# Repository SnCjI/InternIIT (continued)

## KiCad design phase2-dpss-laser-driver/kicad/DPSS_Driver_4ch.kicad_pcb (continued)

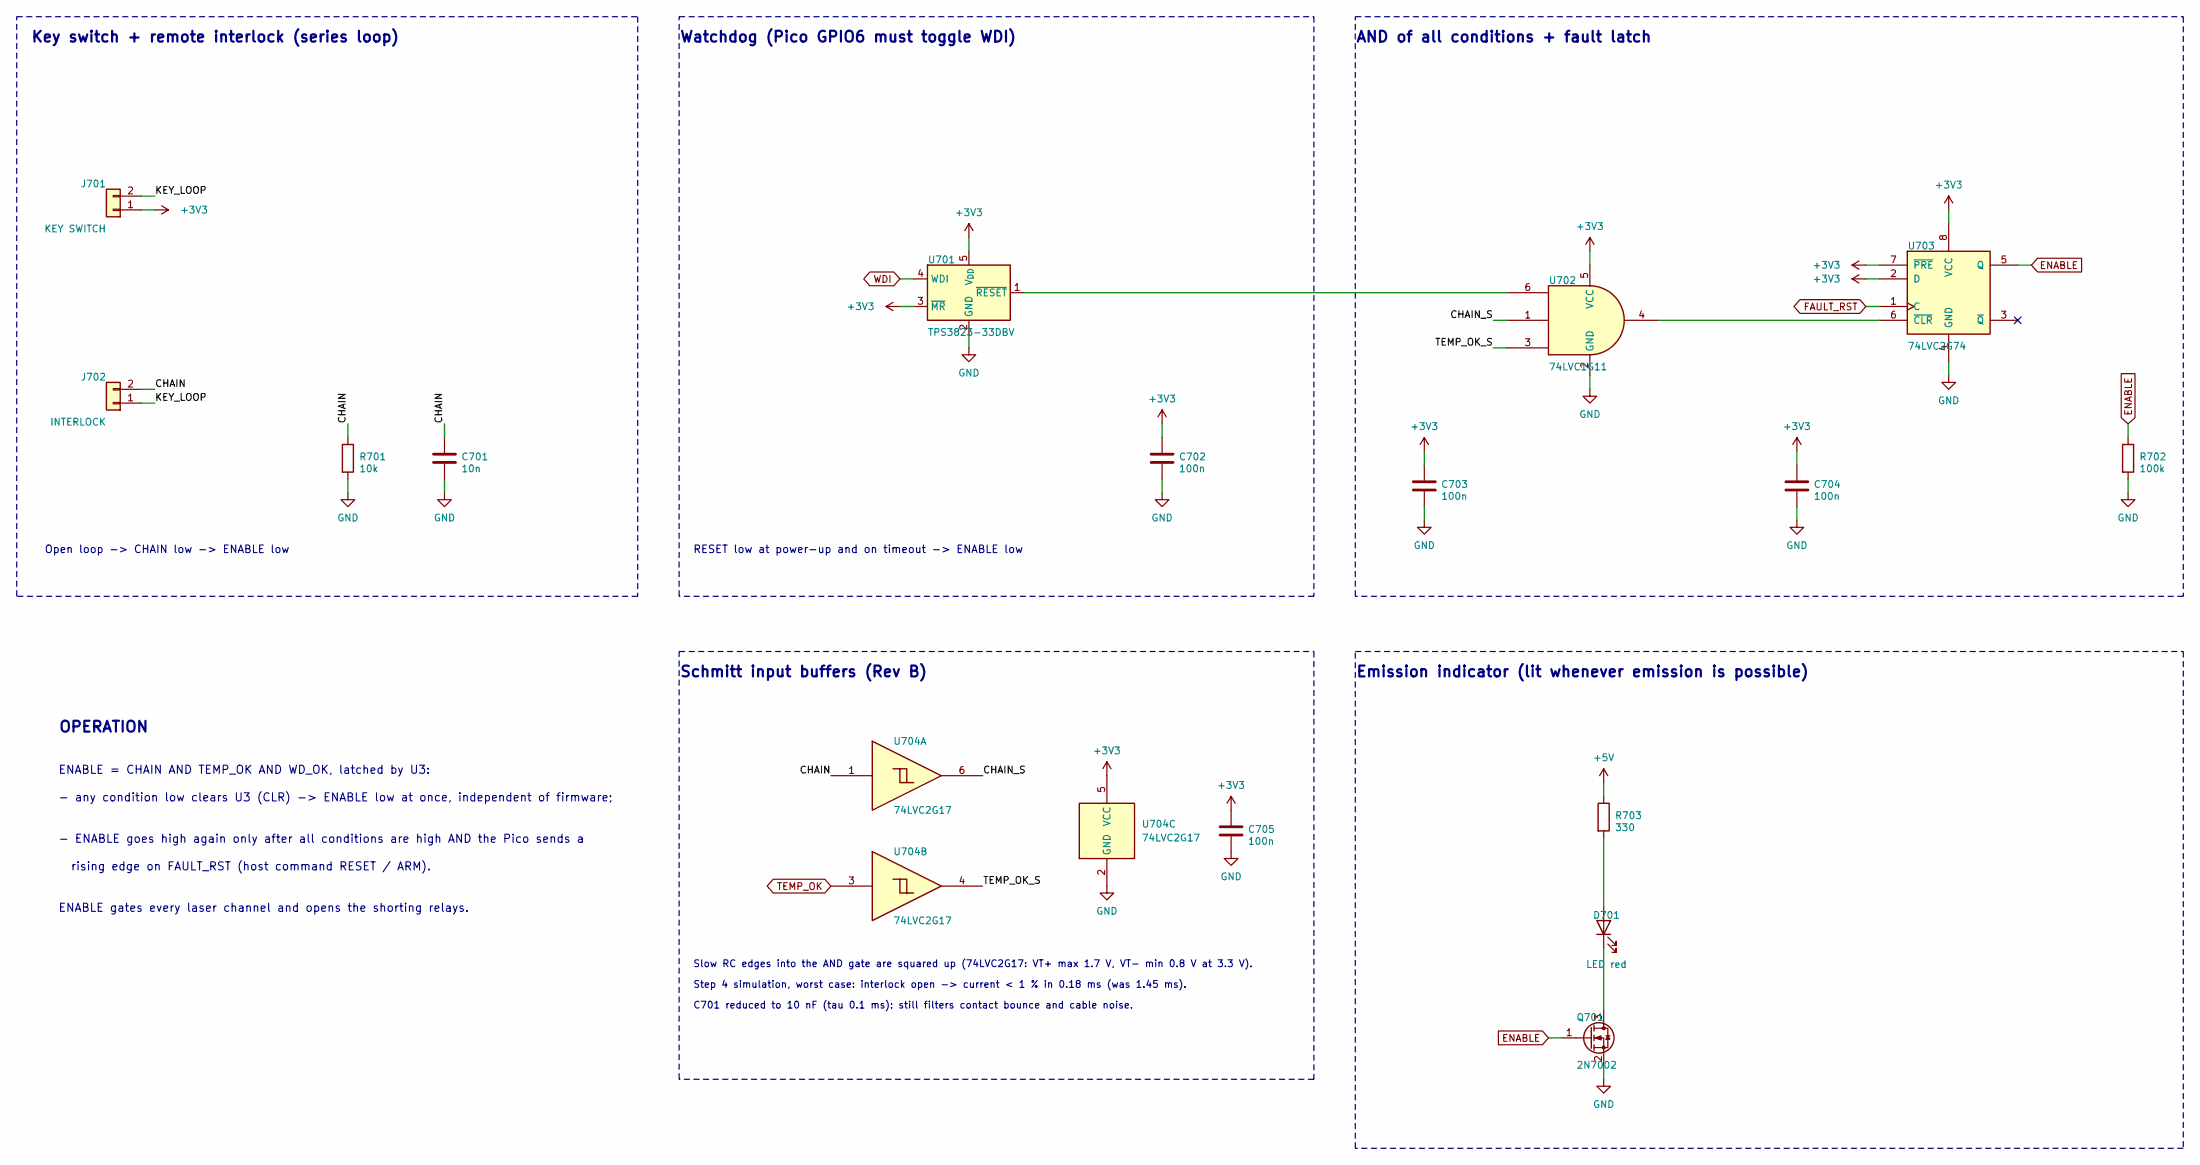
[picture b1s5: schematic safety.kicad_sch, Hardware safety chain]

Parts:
C701: 10n; C_0805_2012Metric
C702, C703, C704, C705: 100n; C_0805_2012Metric
D701: LED red; LED_0805_2012Metric
J701: KEY SWITCH; JST_XH_B2B-XH-A_1x02_P2.50mm_Vertical
J702: INTERLOCK; JST_XH_B2B-XH-A_1x02_P2.50mm_Vertical
Q701: 2N7002; SOT-23
R701: 10k; R_0805_2012Metric
R702: 100k; R_0805_2012Metric
R703: 330; R_0805_2012Metric
U701: TPS3823-33DBV; SOT-23-5
U702: 74LVC1G11; SOT-23-6
U703: 74LVC2G74; VSSOP-8_2.3x2mm_P0.5mm
U704: 74LVC2G17; SOT-23-6

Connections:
+3V3: C702.1, C703.1, C704.1, C705.1, J701.1, U701.3 (~MR), U701.5 (V_{DD}), U702.5 (VCC), U703.2 (D), U703.7 (~PRE), U703.8 (VCC), U704.5 (VCC); also elsewhere on the board
+5V: R703.1; also elsewhere on the board
/Safety/CHAIN: C701.1, J702.2, R701.1, U704.1
/Safety/CHAIN_S: U702.1, U704.6
/Safety/KEY_LOOP: J701.2, J702.1
/Safety/TEMP_OK_S: U702.3, U704.4
ENABLE: Q701.1 (G), R702.1, U703.5 (Q); also elsewhere on the board
FAULT_RST: U703.1 (C); also elsewhere on the board
GND: C701.2, C702.2, C703.2, C704.2, C705.2, Q701.2 (S), R701.2, R702.2, U701.2 (GND), U702.2 (GND), U703.4 (GND), U704.2 (GND); also elsewhere on the board
unnamed: D701.2 (A), R703.2
unnamed: D701.1 (K), Q701.3 (D)
unnamed: U701.1 (~RESET), U702.6
unnamed: U702.4, U703.6 (~CLR)
TEMP_OK: U704.3; also elsewhere on the board
WDI: U701.4 (WDI); also elsewhere on the board

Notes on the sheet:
OPERATION
AND of all conditions + fault latch
Emission indicator (lit whenever emission is possible)
- any condition low clears U3 (CLR) -> ENABLE low at once, independent of firmware;
rising edge on FAULT_RST (host command RESET / ARM).
ENABLE gates every laser channel and opens the shorting relays.
ENABLE = CHAIN AND TEMP_OK AND WD_OK, latched by U3:
Watchdog (Pico GPIO6 must toggle WDI)
RESET low at power-up and on timeout -> ENABLE low
Open loop -> CHAIN low -> ENABLE low
Key switch + remote interlock (series loop)
- ENABLE goes high again only after all conditions are high AND the Pico sends a
Schmitt input buffers (Rev B)
Slow RC edges into the AND gate are squared up (74LVC2G17: VT+ max 1.7 V, VT- min 0.8 V at 3.3 V).
Step 4 simulation, worst case: interlock open -> current < 1 % in 0.18 ms (was 1.45 ms).
C701 reduced to 10 nF (tau 0.1 ms): still filters contact bounce and cable noise.

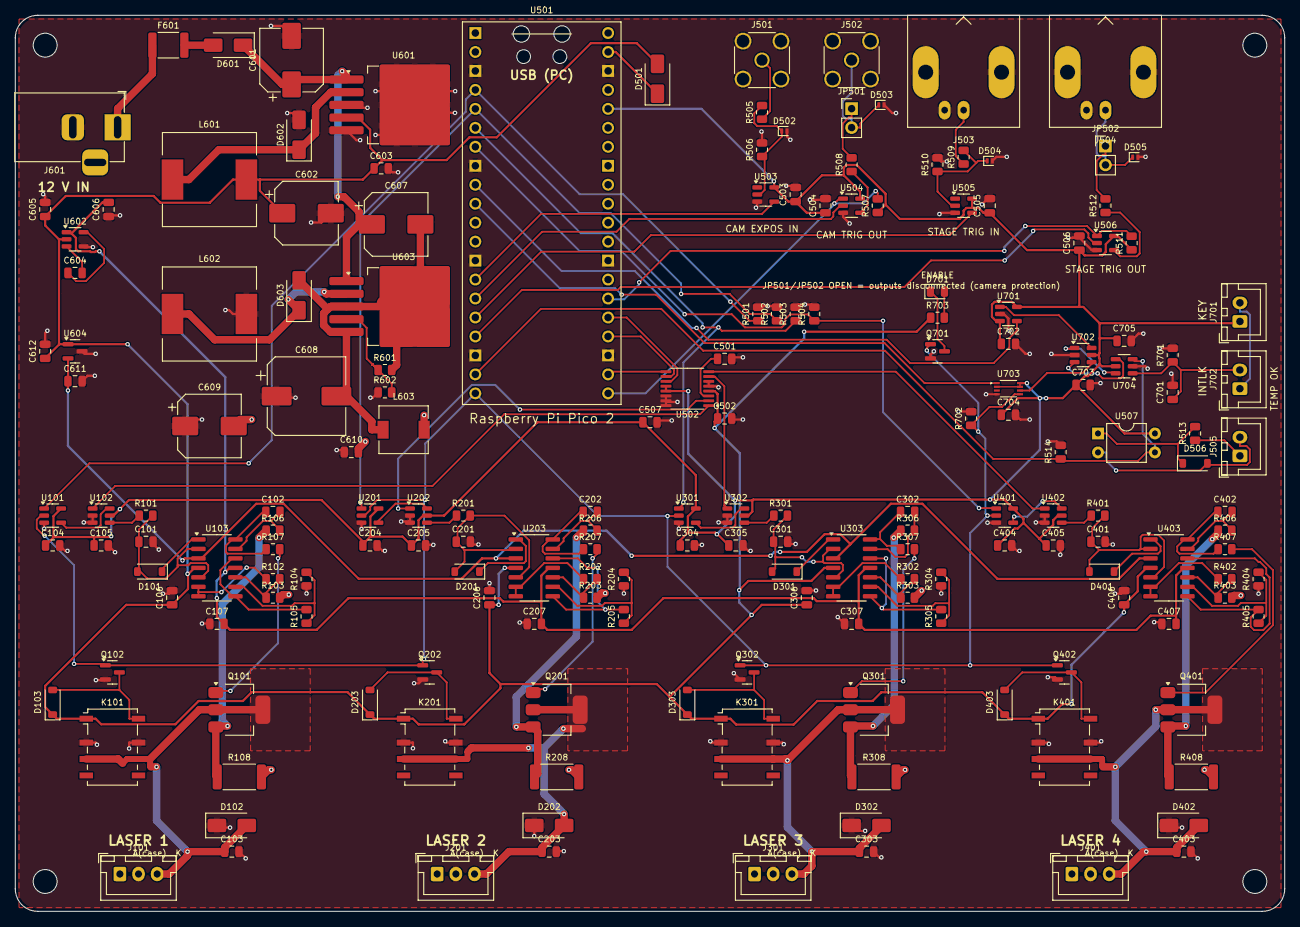
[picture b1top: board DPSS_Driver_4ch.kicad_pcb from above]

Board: 4 copper layers, 170.0 x 120.0 mm, 187 parts (0 on the bottom side), 115 nets.

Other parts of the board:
H1, H2, H3, H4: M3; MountingHole_3.2mm_M3

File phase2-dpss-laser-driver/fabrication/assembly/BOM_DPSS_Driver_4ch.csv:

Qty,Value,Footprint,References
8,2.2n C0G,Capacitor_SMD:C_0805_2012Metric,C101 C102 C201 C202 C301 C302 C401 C402
4,1n,Capacitor_SMD:C_0805_2012Metric,C103 C203 C303 C403
30,100n,Capacitor_SMD:C_0805_2012Metric,C104 C105 C106 C107 C204 C205 C206 C207 C304 C305 C306 C307 C404 C405 C406 C407 C501 C502 C503 C504 C505 C506 C507 C603 C610 C612 C702 C703 C704 C705
1,10n,Capacitor_SMD:C_0805_2012Metric,C701
1,100u 25V,Capacitor_SMD:CP_Elec_8x10,C601
2,220u 10V,Capacitor_SMD:CP_Elec_8x10,C602 C609
4,1u,Capacitor_SMD:C_0805_2012Metric,C604 C605 C606 C611
1,100u 35V,Capacitor_SMD:CP_Elec_8x10,C607
1,470u 10V,Capacitor_SMD:CP_Elec_10x10,C608
9,1N4148W,Diode_SMD:D_SOD-123,D101 D103 D201 D203 D301 D303 D401 D403 D506
5,SS14,Diode_SMD:D_SMA,D102 D202 D302 D402 D501
2,PESD3V3S1UL,Diode_SMD:D_SOD-882,D502 D503
2,PESD5V0L1UL,Diode_SMD:D_SOD-882,D504 D505
3,SS34,Diode_SMD:D_SMA,D601 D602 D603
1,LED red,LED_SMD:LED_0805_2012Metric,D701
1,2 A,Fuse:Fuse_1812_4532Metric,F601
4,LASER (JST-XH),Connector_JST:JST_XH_B3B-XH-A_1x03_P2.50mm_Vertical,J101 J201 J301 J401
2,SMA,Connector_Coaxial:SMA_Amphenol_132134_Vertical,J501 J502
2,BNC,Connector_Coaxial:BNC_Amphenol_B6252HB-NPP3G-50_Horizontal,J503 J504
1,TEMP_OK IN,Connector_JST:JST_XH_B2B-XH-A_1x02_P2.50mm_Vertical,J505
1,12 V IN,Connector_BarrelJack:BarrelJack_Horizontal,J601
1,KEY SWITCH,Connector_JST:JST_XH_B2B-XH-A_1x02_P2.50mm_Vertical,J701
1,INTERLOCK,Connector_JST:JST_XH_B2B-XH-A_1x02_P2.50mm_Vertical,J702
2,OPEN,Connector_PinHeader_2.54mm:PinHeader_1x02_P2.54mm_Vertical,JP501 JP502
4,G6K-2F-Y 5V,Relay_SMD:Relay_DPDT_Omron_G6K-2F-Y,K101 K201 K301 K401
2,33u 3A,Inductor_SMD:L_12x12mm_H8mm,L601 L602
1,10u 3A,Inductor_SMD:L_6.3x6.3_H3,L603
4,NDT3055L,Package_TO_SOT_SMD:SOT-223-3_TabPin2,Q101 Q201 Q301 Q401
5,2N7002,Package_TO_SOT_SMD:SOT-23,Q102 Q202 Q302 Q402 Q701
10,1k,Resistor_SMD:R_0805_2012Metric,R101 R106 R201 R206 R301 R306 R401 R406 R509 R513
8,100k 0.1%,Resistor_SMD:R_0805_2012Metric,R102 R104 R202 R204 R302 R304 R402 R404
8,16k 0.1%,Resistor_SMD:R_0805_2012Metric,R103 R105 R203 R205 R303 R305 R403 R405
4,47,Resistor_SMD:R_0805_2012Metric,R107 R207 R307 R407
4,1R 0.1% 1W,Resistor_SMD:R_2512_6332Metric,R108 R208 R308 R408
7,100k,Resistor_SMD:R_0805_2012Metric,R501 R502 R503 R504 R506 R510 R702
3,100,Resistor_SMD:R_0805_2012Metric,R505 R508 R512
4,10k,Resistor_SMD:R_0805_2012Metric,R507 R511 R514 R701
1,1k 1%,Resistor_SMD:R_0805_2012Metric,R601
1,1.69k 1%,Resistor_SMD:R_0805_2012Metric,R602
1,330,Resistor_SMD:R_0805_2012Metric,R703
4,74LVC1G08,Package_TO_SOT_SMD:SOT-23-5,U101 U201 U301 U401
4,TS5A3159,Package_TO_SOT_SMD:SOT-23-6,U102 U202 U302 U402
4,OPA4197,Package_SO:SOIC-14_3.9x8.7mm_P1.27mm,U103 U203 U303 U403
1,Raspberry Pi Pico 2,Module:RaspberryPi_Pico_Common_Unspecified,U501
1,DAC8565,Package_SO:TSSOP-16_4.4x5mm_P0.65mm,U502
2,74LVC1G17,Package_TO_SOT_SMD:SOT-23-5,U503 U505
2,74LVC1G125,Package_TO_SOT_SMD:SOT-23-5,U504 U506
1,PC817,Package_DIP:DIP-4_W7.62mm,U507
1,LM2596S-5.0,Package_TO_SOT_SMD:TO-263-5_TabPin3,U601
1,TPS60403,Package_TO_SOT_SMD:SOT-23-5,U602
1,LM2596S-ADJ,Package_TO_SOT_SMD:TO-263-5_TabPin3,U603
1,REF3025,Package_TO_SOT_SMD:SOT-23,U604
1,TPS3823-33DBV,Package_TO_SOT_SMD:SOT-23-5,U701
1,74LVC1G11,Package_TO_SOT_SMD:SOT-23-6,U702
1,74LVC2G74,Package_SO:VSSOP-8_2.3x2mm_P0.5mm,U703
1,74LVC2G17,Package_TO_SOT_SMD:SOT-23-6,U704

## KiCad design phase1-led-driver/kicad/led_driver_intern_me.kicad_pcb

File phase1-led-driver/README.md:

# Phase 1 — Five-Channel Multispectral LED Driver

**ESP32 PWM control · MEAN WELL LDD-H constant-current modules · KiCad 10 · Proteus / ngspice**

Phase 1 of the internship: a driver that powers five high-power COB LEDs (UV, Blue, Green, Red and NIR) for multispectral microscopy. Each color can be dimmed independently from a PC. The design was taken from requirements to a fabrication-ready PCB and verified in simulation. No hardware was built.

Full report (IEEE format): [`report/Multispectral_LED_Driver_Phase1_Report_IEEE.pdf`](report/Multispectral_LED_Driver_Phase1_Report_IEEE.pdf)

<p align="center">
  
  <br><em>One channel k: ESP32 PWM → NPN buffer → LDD-H constant-current module → COB LED. There are five of these.</em>
</p>

---

## How it works

High-power LEDs have to be driven with **constant current**, not constant voltage. Their forward voltage changes with temperature and from part to part, so a fixed voltage would give each channel a different brightness and could cause thermal runaway.

The design splits the job in two:

- **The LDD-H module regulates the current.** This is a MEAN WELL step-down constant-current driver (350, 500 or 700 mA versions). It holds the LED current steady whatever happens to the supply.
- **The ESP32 decides how long the current flows.** Its LEDC hardware peripheral produces a 500 Hz, 10-bit PWM signal on each channel (GPIO 4, 5, 18, 19, 21). The LED is either fully on at its rated current or fully off, so the **average** current is

  **I<sub>avg</sub> = D · I<sub>on</sub>**, where D is the duty cycle.

A P2N2222A transistor sits between each GPIO and the LDD-H DIM input. It isolates the 3.3 V microcontroller from the module, but it also **inverts** the signal: GPIO high → DIM pulled low → LED off. The firmware compensates by writing `1023 − duty`.

A nice side effect of PWM dimming is that the LED always runs at its full rated current while it is on, so its emission spectrum does not shift as the brightness changes. That matters for multispectral imaging.

---

## Step by step: what was done

### Step 1 — Requirements and architecture

I wrote down eight requirements (R1–R8) and linked each one to a test case: five independent channels, 0–100 % intensity, constant current (350–700 mA), a single 12 V supply with a 3.3 V logic interface, a serial command interface, hardware PWM with less than 1 LSB of timing error, a clean two-layer PCB, and thermal margin for every part.

### Step 2 — Schematic and design review

The schematic repeats the same block five times: a 1 kΩ base resistor, a P2N2222A transistor, a 6-pin header for the LDD-H module (J0–J4), and the LED output pads (D0–D4). An 8-pin header (J5) brings in +12 V, GND and the five PWM signals.

Before drawing the PCB I reviewed every connection against the datasheets. **This review found four groups of defects**, two of which would have made the board useless:

| Problem found | Fix |
|---|---|
| The PCB file I inherited contained only graphics (0 pads, 0 nets) | Regenerated the board from the schematic and routed it from scratch |
| The generic NPN symbol used B-C-E pin order, but the P2N2222A TO-92 package is **C-B-E** | Changed to the correct symbol, so base and collector are no longer swapped |
| LEDs D0–D4 were wired with **reversed polarity** | Swapped the VOUT+/VOUT− labels |
| Net-label errors (global vs. local, an undefined net, duplicate connectors) | Unified the labels and aligned references with the PCB |

Result: **KiCad ERC, 0 errors.**

### Step 3 — PCB layout

- Two layers, FR-4, 1.6 mm, 1 oz copper, **118 × 43 mm**, through-hole parts only for easy hand assembly
- Each channel sits in an identical 20 mm cell: header, transistor, resistor, LED
- +12 V bus on top and ground bus on the bottom, both 0.8 mm wide
- No vias needed: 77 pads, 91 track segments, 27 nets
- Silkscreen labels for every J5 pin and every channel color

Result: **KiCad DRC, 0 violations, 0 unconnected items, 0 schematic-parity differences.**

### Step 4 — Firmware

[`firmware/firmware_intern/firmware_intern.ino`](firmware/firmware_intern/firmware_intern.ino) is an Arduino sketch for the ESP32 (Arduino core 3.x; the code has a note on the 2.x API). It accepts text commands at 115200 baud:

| Command | Effect |
|---|---|
| `SET <ch 0–4> <duty 0–100>` | Set one channel's brightness |
| `ALL <duty 0–100>` | Set every channel |
| `OFF` | Turn every channel off |
| `STATUS` | Show name, GPIO and duty of each channel |
| `HELP` | List the commands |

All channels start at `MAX_DUTY`, so the LEDs turn off as soon as the firmware runs. The sketch was run in the **Velxio ESP32 simulator** and passed every command test.

### Step 5 — Circuit simulation

The LDD-H is a sealed module with no public SPICE model, so I simulated each half of the channel with an equivalent circuit, then both halves together:

**a) Constant-current regulation.** A classic two-transistor current limiter was simulated in Proteus while the supply was swept from 8 V to 15 V. The current stayed at **0.48–0.50 A** (within ±0.01 A, which is the resolution of the simulated ammeter).

**b) PWM buffer switching.** The transistor stage turns the 0–3.3 V PWM into a clean 0–5 V inverted DIM signal. The worst edge delay is about **0.17 µs**, under 0.1 LSB of the 10-bit PWM period (1 LSB = 1.96 µs), so it does not affect brightness resolution.

**c) Duty cycle → LED current.** Both halves were joined in one test bench and run at D = 0, 5, 20, 50, 80 and 100 %. The on-current is always 363 mA. Only the fraction of time it flows changes, and the average follows **I<sub>avg</sub> = D · I<sub>on</sub>** with a constant offset of only −0.7 mA (about 2 LSB). An ngspice sweep from 0 to 100 % confirms the same straight line.

### Step 6 — Thermal check and test report

Every part on the board runs far below its rating: the transistors dissipate less than 2 mW each, and the 0.8 mm power traces heat up about 4 °C at full load. The real heat sources are the COB LEDs (about 3 W each), which have to be mounted off-board on a heatsink.

The test report has **15 test cases; 14 pass**. The one "fail" (TC-14) is intentional. It shows that the discrete limiter used for simulation would overheat as real hardware (5.5 W in a TO-92 package), which is exactly why the real design uses the LDD-H module.

### Step 7 — Fabrication package

Everything needed to order the board is in [`fabrication/`](fabrication/). For one-click ordering, the ready-made package is [`LED_Driver_5ch_Fabrication_Package_v1.0.zip`](fabrication/LED_Driver_5ch_Fabrication_Package_v1.0.zip).

| Folder | Content |
|---|---|
| `gerbers/` | Gerber X2 (copper, mask, paste, silkscreen, outline), job file, Excellon PTH + NPTH |
| `assembly/` | BOM (5× P2N2222A, 5× 1 kΩ, 5× 1×6 header, 1× 1×8 header, LED positions) and placement file |
| `docs/` | Schematic PDF, Gerber preview, DRC screenshot |
| `README_fabrication.txt` | Board specs and **assembly warnings**: use the P2N2222A (not PN2222A), the square pad is the LED cathode, and don't fit 5 mm LEDs while an LDD-H is installed |

---

## Future objectives for Phase 1

- [ ] **Board v1.1:** add a pull-up (for example 10 kΩ to 3.3 V) on each PWM input. Because the buffer inverts the signal, the LEDs currently run at full current while the ESP32 is booting or being flashed, and this matters most for the UV channel.
- [ ] **Board v1.1:** replace the 5 mm LED footprints (D0–D4) with 2-pin terminal blocks for the COB LED leads.
- [ ] Measure the LDD-H DIM pull-up current and check the 500 Hz dimming linearity on real hardware.
- [ ] Fabricate and assemble the board, and repeat the PWM edge measurements with an oscilloscope.
- [ ] Characterize the LED current of each channel with the real LDD-H modules, and compensate the −0.7 mA offset in firmware if needed.
- [ ] Design the LED heatsink and the optical coupling to the microscope.
- [ ] Sync camera exposures to an integer number of 2 ms PWM periods to avoid frame-to-frame flicker.

---

## Folder contents

| Path | What is inside |
|---|---|
| `report/` | Phase 1 report, IEEE format (PDF, 9 pages) |
| `kicad/` | `led_driver_intern_me.kicad_pro / .kicad_sch / .kicad_pcb`. Open with **KiCad 10**. |
| `fabrication/` | Gerbers, drill, BOM, positions, docs, and the full package as a ZIP |
| `firmware/firmware_intern/` | ESP32 Arduino sketch |
| `simulation/` | Proteus project for the PWM/DIM transient (`.pdsprj`), screenshots `sim_00`–`sim_05`, firmware simulator logs `fw_01`–`fw_03`, and `PWM_LED_Current_Control/` (Proteus project, ngspice netlist, CSV data, plots and its own README) |

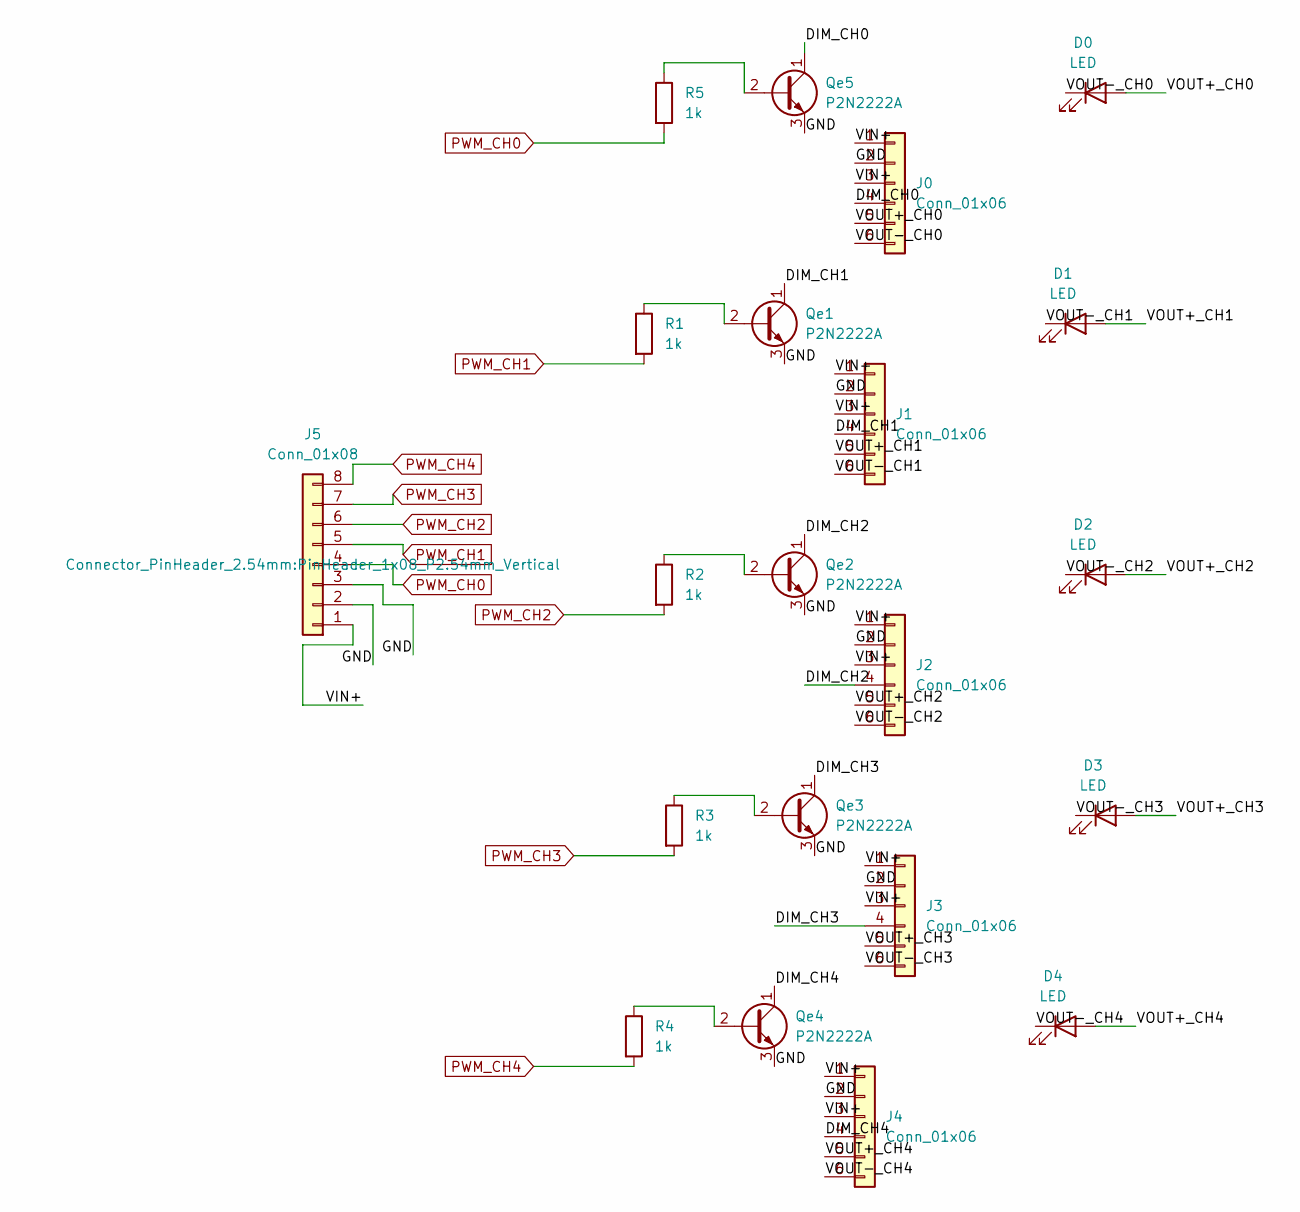
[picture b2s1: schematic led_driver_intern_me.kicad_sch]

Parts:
D0, D1, D2, D3, D4: LED; LED_D5.0mm
J0, J1, J2, J3, J4: Conn_01x06; PinHeader_1x06_P2.54mm_Vertical
J5: Conn_01x08; PinHeader_1x08_P2.54mm_Vertical
Qe1, Qe2, Qe3, Qe4, Qe5: P2N2222A; TO-92_Inline
R1, R2, R3, R4, R5: 1k; R_Axial_DIN0207_L6.3mm_D2.5mm_P10.16mm_Horizontal

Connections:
/DIM_CH0: J0.4, Qe5.1 (C)
/DIM_CH1: J1.4, Qe1.1 (C)
/DIM_CH2: J2.4, Qe2.1 (C)
/DIM_CH3: J3.4, Qe3.1 (C)
/DIM_CH4: J4.4, Qe4.1 (C)
/GND: J0.2, J1.2, J2.2, J3.2, J4.2, J5.2, J5.3, Qe1.3 (E), Qe2.3 (E), Qe3.3 (E), Qe4.3 (E), Qe5.3 (E)
/VIN+: J0.1, J0.3, J1.1, J1.3, J2.1, J2.3, J3.1, J3.3, J4.1, J4.3, J5.1
/VOUT+_CH0: D0.2 (A), J0.5
/VOUT+_CH1: D1.2 (A), J1.5
/VOUT+_CH2: D2.2 (A), J2.5
/VOUT+_CH3: D3.2 (A), J3.5
/VOUT+_CH4: D4.2 (A), J4.5
/VOUT-_CH0: D0.1 (K), J0.6
/VOUT-_CH1: D1.1 (K), J1.6
/VOUT-_CH2: D2.1 (K), J2.6
/VOUT-_CH3: D3.1 (K), J3.6
/VOUT-_CH4: D4.1 (K), J4.6
unnamed: Qe1.2 (B), R1.1
unnamed: Qe2.2 (B), R2.1
unnamed: Qe3.2 (B), R3.1
unnamed: Qe4.2 (B), R4.1
unnamed: Qe5.2 (B), R5.1
PWM_CH0: J5.4, R5.2
PWM_CH1: J5.5, R1.2
PWM_CH2: J5.6, R2.2
PWM_CH3: J5.7, R3.2
PWM_CH4: J5.8, R4.2

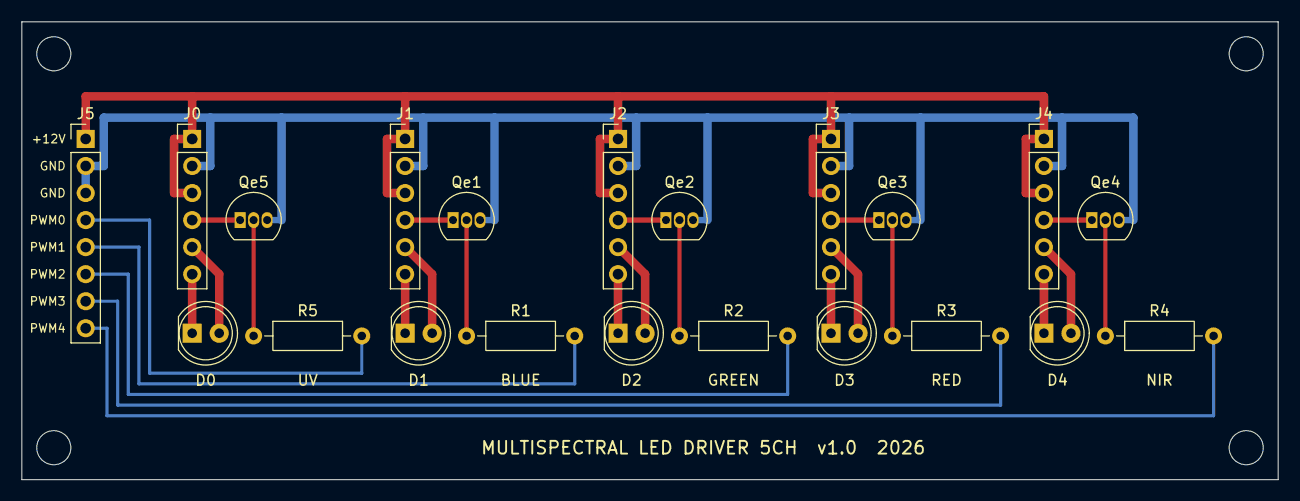
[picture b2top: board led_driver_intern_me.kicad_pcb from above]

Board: 2 copper layers, 118.0 x 43.0 mm, 25 parts (0 on the bottom side), 27 nets.

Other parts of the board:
H1, H2, H3, H4: MountingHole_3.2mm_M3

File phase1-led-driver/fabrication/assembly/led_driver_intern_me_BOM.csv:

"Item";"Designator";"Footprint";"Quantity";"Value";"Supplier and ref";
1;"D0, D1, D2, D3, D4";"LED_D5.0mm";5;"LED";;;
2;"J0, J1, J2, J3, J4";"PinHeader_1x06_P2.54mm_Vertical";5;"Conn_01x06";;;
3;"J5";"PinHeader_1x08_P2.54mm_Vertical";1;"Conn_01x08";;;
4;"Qe1, Qe2, Qe3, Qe4, Qe5";"TO-92_Inline";5;"P2N2222A";;;
5;"R1, R2, R3, R4, R5";"R_Axial_DIN0207_L6.3mm_D2.5mm_P10.16mm_Horizontal";5;"1k";;;

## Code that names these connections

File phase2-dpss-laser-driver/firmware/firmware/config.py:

# DPSS 4-channel laser driver - Pico 2 (RP2350) firmware configuration
# Pin numbers are GPIO numbers and match the KiCad schematic (controller.kicad_sch).

FW_VERSION = "DPSS4CH-FW 0.1 (Phase 2, simulation build)"
SYS_CLK_HZ = 150_000_000          # RP2350 default system clock; PIO runs at this clock (divider 1)

# ---- GPIO map (Pico 2 pin -> GPIO) ----
PIN_LASER_ON_BASE = 2             # GPIO2..GPIO5 = LASER_ON1..4 (100 k pull-downs on the board)
N_CH = 4
PIN_WDI = 6                       # TPS3823 watchdog input (toggle < 1.6 s)
PIN_FAULT_RST = 7                 # clock of the 74LVC2G74 fault latch (re-arm ENABLE)
PIN_CAM_EXPOS = 10                # camera "Status Expos" (input, via 74LVC1G17)
PIN_CAM_TRIG = 11                 # camera exposure trigger (output, via 74LVC1G125)
PIN_STAGE_IN = 12                 # stage in-position trigger (input, via 74LVC1G17)
PIN_STAGE_OUT = 13                # trigger to the stage controller (output, via 74LVC1G125)
PIN_TEMP_OK = 14                  # temperature-OK from the lab's temperature unit (opto, active high)
PIN_ENABLE = 15                   # hardware safety chain output (read only)
PIN_CAM_OE_N = 16                 # camera trigger buffer enable, active low (pull-up = disabled)
PIN_DAC_SYNC = 17                 # DAC8565 SYNC (SPI0 CSn, driven by software)
PIN_DAC_SCLK = 18                 # SPI0 SCK
PIN_DAC_DIN = 19                  # SPI0 TX
PIN_STAGE_OE_N = 20               # stage trigger buffer enable, active low

# ---- current channel (hardware, see Step 2) ----
DAC_VREF_V = 2.5                  # DAC8565 internal reference -> full scale 2.5 V
GM_MA_PER_V = 160.0               # transconductance of the current sink: I = 160 mA/V * V_DAC
I_HW_CLAMP_MA = 400.0             # hardware clamp (VREF_LIM = 2.5 V); DJ532-40 absolute maximum
I_LIMIT_DEFAULT_MA = 330.0        # per-unit firmware limit until the unit is calibrated
                                  # (datasheet: 40 mW typ. at 330 mA; 50 mW max. reached ~382 mA)
RAMP_MIN_MS = 100                 # requirement E5: 0 -> limit takes at least 100 ms
RAMP_STEP_MS = 2                  # ramp update period

# ---- timing defaults (can be changed with commands) ----
SETTLE_US_DEFAULT = 2000          # stage in-position -> laser ON (mechanical settling)
LEAD_US_DEFAULT = 5000            # laser ON -> camera trigger (>= 5 tau of the DPSS output)
TRIG_US_DEFAULT = 10              # camera trigger pulse width (mode B)
STAGE_PULSE_US_DEFAULT = 100      # pulse to the stage controller
MAX_EMIT_MS_DEFAULT = 2000        # laser ON longer than this without end of exposure -> FAULT
HEARTBEAT_MS = 3000               # no command from the PC for this long while emitting -> FAULT
WDI_PERIOD_MS = 200               # watchdog toggle period (TPS3823-33 timeout 1.6 s typ.)

# ---- camera protection (PCO.panda: 3.3 V LVTTL trigger input) ----
CAM_TRIG_MAX_US = 100             # longest trigger pulse the firmware will generate. The camera
                                  # exposure must last longer than the trigger pulse (the PIO
                                  # waits for Status Expos to rise after the pulse; an exposure
                                  # that ends inside the pulse is caught by EXPOSURE_TIMEOUT)
CAM_MIN_PERIOD_US = 25_000        # shortest time between triggers (panda 4.2 bi full frame ~40 fps)

LIMITS_FILE = "limits.json"       # per-unit current limits stored in the Pico flash
